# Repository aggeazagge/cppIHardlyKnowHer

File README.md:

# Autonomonomous car by C++, I hardly know her

A school project building autonomous vehicles that drive themselves along a
walled track about 1 m wide. The firmware is written in MicroPython for an
ESP32-family board. Each vehicle uses three time-of-flight distance sensors to
stay centered between the walls, a Pololu Motoron motor controller, and a start
module that tells it when to go.

### Code

| Folder | Vehicle | Description |
|---|---|---|
| [snok_1.2](snok_1.2/README.md) | RC car | Ackermann steering with a servo and one drive motor. Detects when it is stuck and reverses out |
| [huggorm_1.0](huggorm_1.0/README.md) | Tracked chassis | Excavator with two tracks, steers by the speed difference between them |

Each folder is a complete firmware. To run one, copy its `config.py`, `main.py`
and `lib/` to the board, for example with Thonny. All tunable values are in `config.py`.

### Components

- VL53L4CX ToF lidar sensor – left and right side sensors
- VL53L0X ToF lidar sensor – front (middle) sensor
- Pololu Motoron M2T550 dual I2C motor controller
- DC-DC step-down converter (1.23–30 V, 1.5 A)
- Slide switch (on-on)
- GT Power B3 battery charger

### PCB-schematics

[Kicad/Bil v 1,0](Kicad/Bil%20v%201,0) contains the KiCad project for the
car's circuit board: the schematic, the PCB layout, and the custom symbol
libraries (`Auto_car_library`, `motron_i2c_3motor`).

### License

See [LICENSE](LICENSE).

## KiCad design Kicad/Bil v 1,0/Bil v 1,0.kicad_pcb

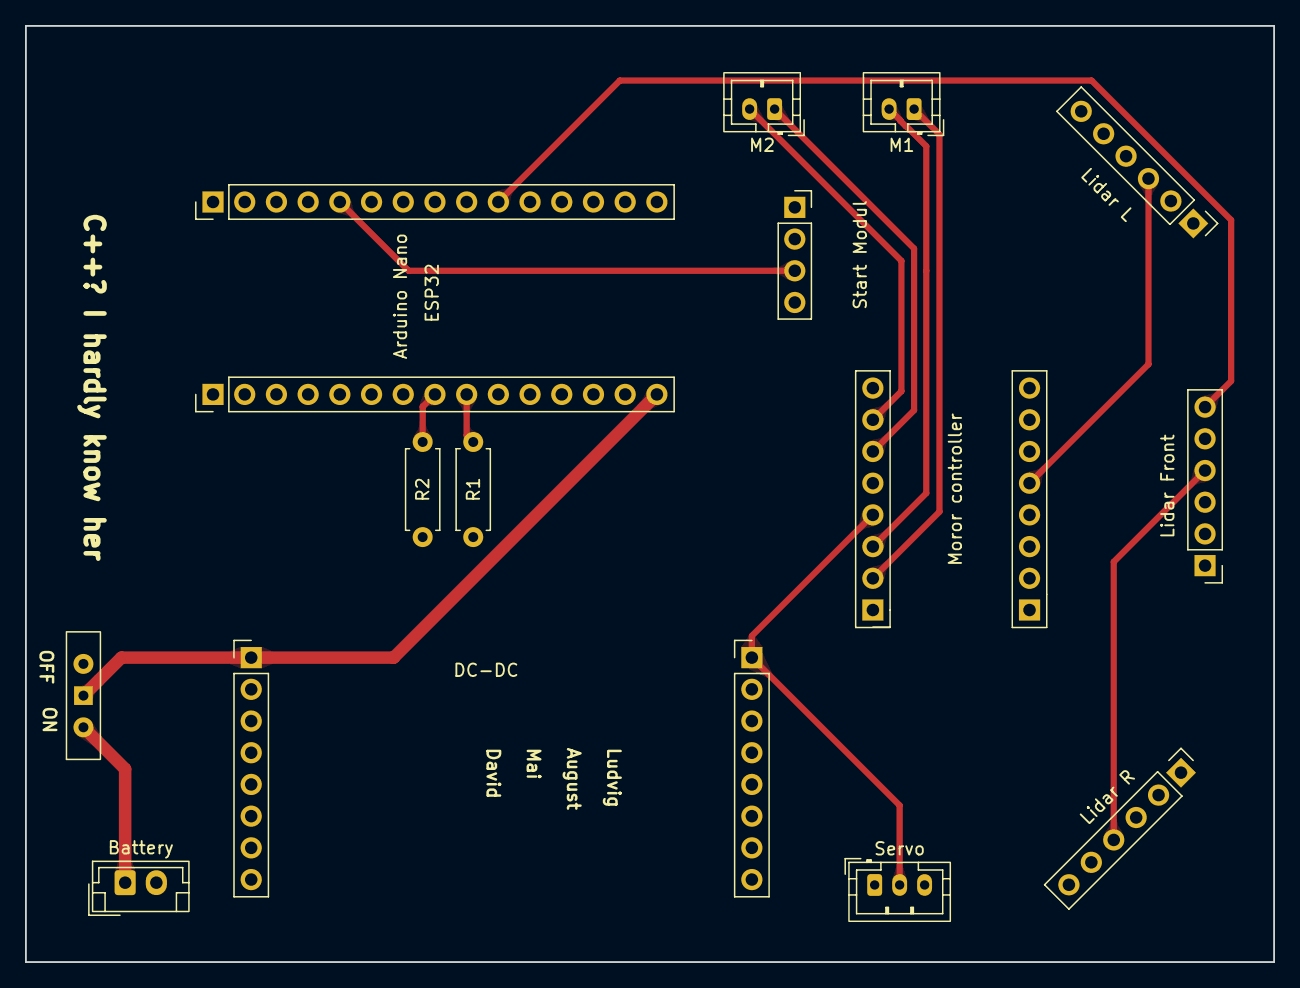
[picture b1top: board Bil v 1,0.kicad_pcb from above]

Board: 4 copper layers, 100.0 x 75.0 mm, 15 parts (0 on the bottom side), 17 nets.

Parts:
Arduino Nano: Analog; PinHeader_1x15_P2.54mm_Vertical
Battery: Battery; JST_EH_B2B-EH-A_1x02_P2.50mm_Vertical
DC-DC: DC_DC
ESP32: Digital; PinHeader_1x15_P2.54mm_Vertical
Lidar Front: Lidar_sensor_adafruit_VL53L0X; PinHeader_1x06_P2.54mm_Vertical
Lidar L: Lidar_sensor_adafruit_VL53L0X; PinHeader_1x06_P2.54mm_Vertical
Lidar R: Lidar_sensor_adafruit_VL53L0X; PinHeader_1x06_P2.54mm_Vertical
M1, M2: Motor_DC; JST_PH_B2B-PH-K_1x02_P2.00mm_Vertical
Moror controller: Motron motorcontroller 2 motor
R1, R2: 1,3 kΩ; R_Axial_DIN0207_L6.3mm_D2.5mm_P7.62mm_Horizontal
SW2: power switch; SW_Slide-03_Wuerth-WS-SLTV_10x2.5x6.4_P2.54mm
Servo: Motor_Servo; JST_PH_B3B-PH-K_1x03_P2.00mm_Vertical
Start Modul: Conn_01x04; PinSocket_1x04_P2.54mm_Vertical

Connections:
+3V3: Arduino Nano.2, Lidar Front.1 (Vin), Lidar L.1 (Vin), Lidar R.1 (Vin), Moror controller.7 (Vdd), R1.2, R2.2, Start Modul.1
/*D3: ESP32.10, Lidar Front.6 (Xshut)
/*D5: ESP32.8, Lidar R.6 (Xshut)
/*D9: ESP32.4, Servo.1 (PWM)
/A4/SDA: Arduino Nano.8, Lidar Front.4 (SDA), Lidar L.4 (SDA), Lidar R.4 (SDA), Moror controller.6 (SDA), R2.1
/A5/SCL: Arduino Nano.9, Lidar Front.3 (SCL), Lidar L.3 (SCL), Lidar R.3 (SCL), Moror controller.5 (SCL), R1.1
/D4: ESP32.9, Lidar L.6 (Xshut)
/D8: ESP32.5, Start Modul.3
/DC-DC out: DC-DC.3 (Out_+), Moror controller.12 (Vin), Servo.2 (+)
/M1 +: M1.1 (+), Moror controller.10 (M1b)
/M1 -: M1.2 (-), Moror controller.11 (M1a)
/M2 +: M2.1 (+), Moror controller.14 (M2a)
/M2 -: M2.2 (-), Moror controller.15 (M2b)
/~RESET: Arduino Nano.13, ESP32.13
GND: Arduino Nano.14, Battery.2 (-), DC-DC.2 (in_-), DC-DC.4 (Out_-), ESP32.12, Lidar Front.2 (GND), Lidar L.2 (GND), Lidar R.2 (GND), Moror controller.8 (Gnd), Moror controller.13 (Gnd), Servo.3 (-), Start Modul.2
unnamed: Battery.1 (+), SW2.2 (B)
VCC: Arduino Nano.15, DC-DC.1 (in_+), SW2.1 (C)
